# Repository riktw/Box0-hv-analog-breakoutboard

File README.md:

A breakout board for the Box0 so the Box0 is able to handle higher analog voltages
With this it can handle -33 to +33V on the input and output -33V to +33V as well.

The hardware is simple, 2 switching power supplies to boost the 5V in to +-33V, possible +-35V
After that 2 +-50V 50mA output capable opamps with a gain of 10 and a divide by 10 voltage devider so the analog inputs can handle +-33V as well

An USB port is added to supply the board with 5V as the 5V pin of the Box0 is unable to deliver enough current.
A small example:

10mA at 35V means that, at 100% efficiency, 70mA is needed at 5V, in practise this figure is closer to 90mA
With 2 opamps being capable of delivering 50mA a total of 100mA at 35V is required, meaning 900mA at 5V as input.

Current limit is implemented by using a 1A polyfuse, minimal but better then nothing. 

License: CC-SA-BY 4.0

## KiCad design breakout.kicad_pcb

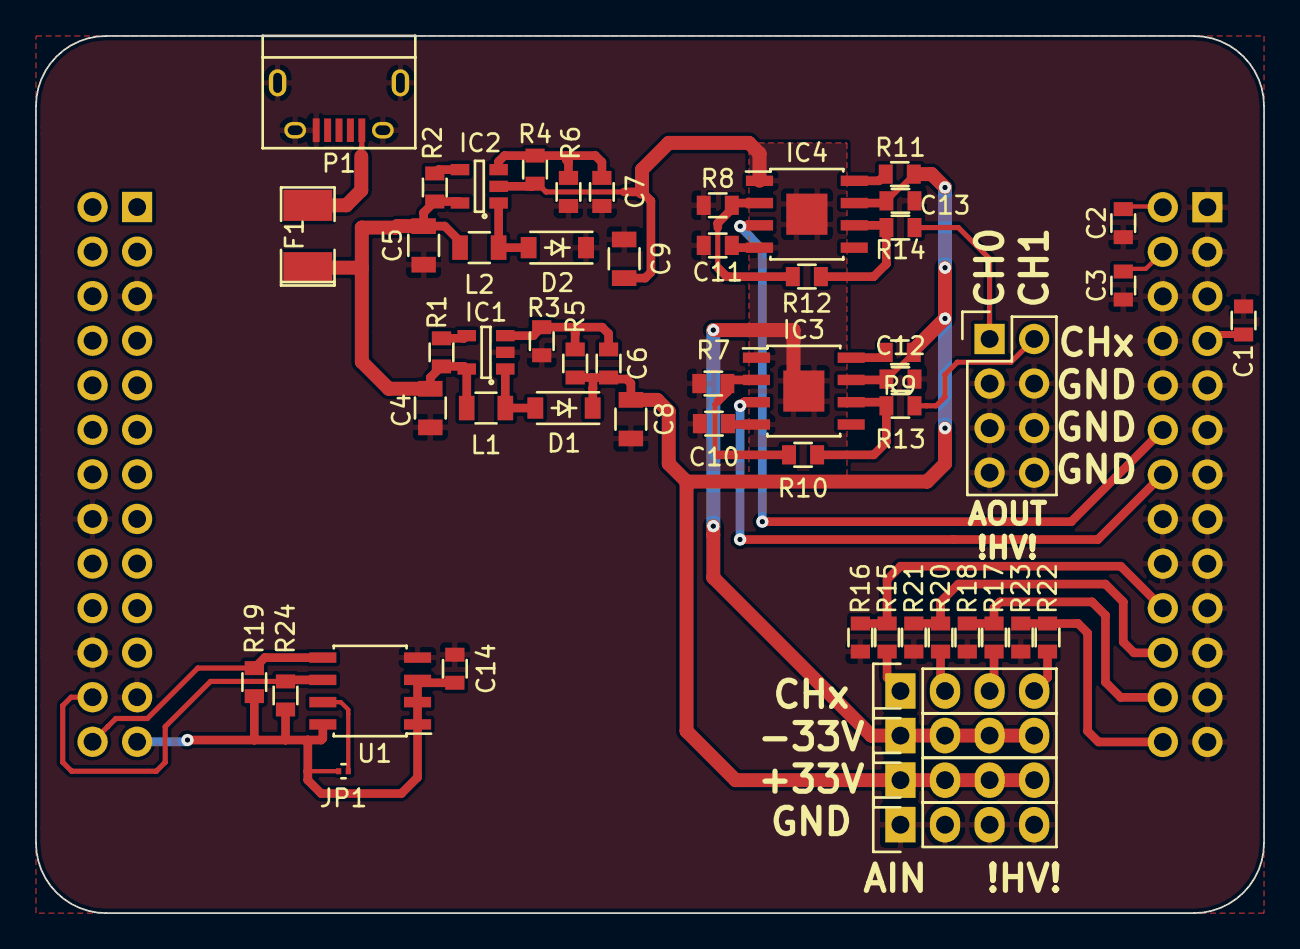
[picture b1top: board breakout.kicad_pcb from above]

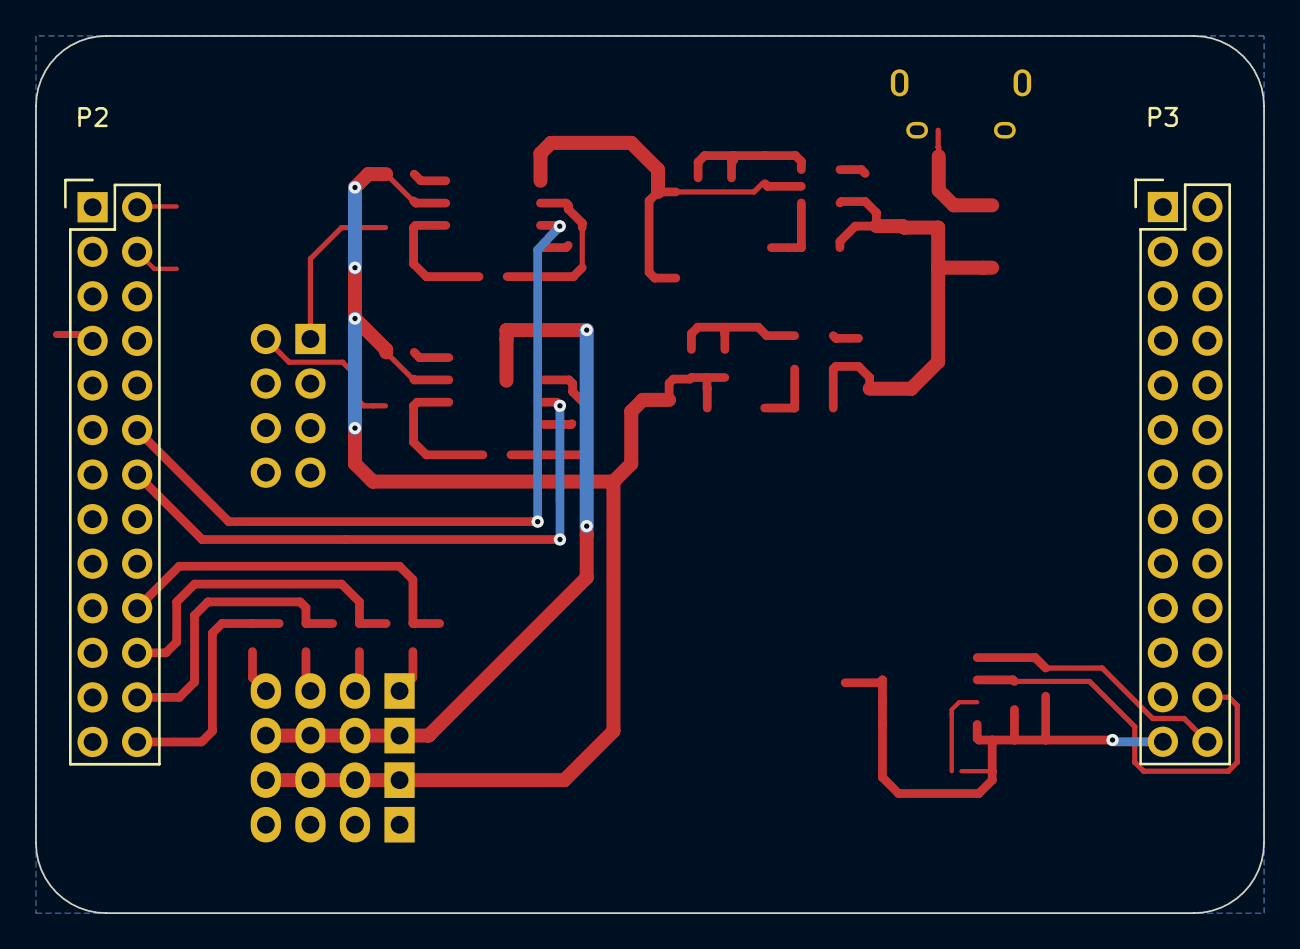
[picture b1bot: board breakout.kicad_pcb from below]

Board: 2 copper layers, 70.0 x 50.0 mm, 57 parts (2 on the bottom side), 36 nets.

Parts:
C1, C2, C3: 100nF; 0603
C4, C5: 4.7u; 0805
C6, C7: 82p; 0603
C8, C9: 10u; 0805
C10, C11, C12, C13, C14: 100n; 0603
D1, D2: MBR0540; SOD-123
F1: F_Small; SMD-1210_Pol
IC1, IC2: LM2733; SOT-23-5
IC3, IC4: OPA454; SOIC-8-3.9*4.9mm_HP_to_P4
JP1: Jumper_NO_Small; C_0201
L1, L2: 10u; 0805
P1: USB_OTG; USB_Micro-B
P2: BASE_BOARD_ANALOG; Pin_Header_Straight_2x13
P3: BASE_BOARD_DIGITAL; Pin_Header_Straight_2x13
P4: CONN_02X04; Pin_Header_Straight_2x04
P5, P6, P7, P8: CONN_01X04; Pin_Header_Straight_1x04
R1, R2: 47K; 0603
R3, R4: 12K; 0603
R5, R6: 309K; 0603
R7, R8, R16, R18, R21, R23: 10K; 0603
R9, R11: 1M; 0603
R10, R12, R15, R17, R20, R22: 91K; 0603
R13, R14: 10R; 0603
R19, R24: 4.7K; 0603
U1: 24C16; SOIC-8_3.9x4.9mm_Pitch1.27mm

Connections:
5V: C4.1, C5.1, F1.1, IC1.5, IC2.5, L1.2, L2.2, R1.1, R2.1
+33V: C6.2, C8.1, C12.1, C13.1, D1.1, IC3.7, IC4.7, P6.1, P6.2, P6.3, P6.4, R5.2, R9.1, R11.1
-33V: C9.2, C10.1, C11.1, IC2.2, IC3.1, IC3.4, IC4.1, IC4.4, P7.1, P7.2, P7.3, P7.4, R4.2
/Box0 Interface/AIN0.0: P2.20, R15.1, R16.2
/Box0 Interface/AIN0.1: P2.22, R20.1, R21.2
/Box0 Interface/AIN0.2: P2.24, R17.1, R18.2
/Box0 Interface/AIN0.3: P2.26, R22.1, R23.2
/Box0 Interface/AOUT0.0: IC4.3, P2.12
/Box0 Interface/AOUT0.1: IC3.3, P2.14
/Box0 Interface/I2C0.SCL: P3.24, R24.2, U1.6
/Box0 Interface/I2C0.SDA: P3.26, R19.2, U1.5
ANALOG_NEG: C3.1, P2.4
ANALOG_POS: C2.1, P2.2
DIGITAL_EXT: C14.1, JP1.1, P3.25, R19.1, R24.1, U1.1, U1.2, U1.3, U1.8
GND: C1.2, C2.2, C3.2, C4.2, C5.2, C7.2, C8.2, C9.1, C10.2, C11.2, C12.2, C13.2, C14.2, D2.1, IC1.2, P1.5, P1.6, P2.1, P2.3, P2.5, P2.6, P2.8, P2.9, P2.10, P2.11, P2.13, P2.15, P2.16, P2.17, P2.18, P2.19, P2.21, P2.23, P2.25, P3.5, P3.16, P3.22, P3.23, P4.3, P4.4, P4.5, P4.6, P4.7, P4.8, P5.1, P5.2, P5.3, P5.4, R3.2, R6.2, R7.1, R8.1, R16.1, R18.1, R21.1, R23.1, U1.4
unnamed: C6.1, IC1.3, R3.1, R5.1
unnamed: C7.1, IC2.3, R4.1, R6.1
unnamed: D1.2, IC1.1, L1.1
unnamed: D2.2, IC2.1, L2.1
unnamed: F1.2, P1.1
unnamed: IC1.4, R1.2
unnamed: IC2.4, R2.2
unnamed: IC3.2, R7.2, R10.2
unnamed: IC3.6, R10.1, R13.2
unnamed: IC3.8, R9.2
unnamed: IC4.2, R8.2, R12.2
unnamed: IC4.6, R12.1, R14.2
unnamed: IC4.8, R11.2
unnamed: JP1.2, U1.7
unnamed: P4.1, R14.1
unnamed: P4.2, R13.1
unnamed: P8.1, R15.2
unnamed: P8.2, R20.2
unnamed: P8.3, R17.2
unnamed: P8.4, R22.2
VREF_EXT: C1.1, P2.7

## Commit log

2016-12-17 First commit, empty breakout board
2016-12-18 Schematic nearly done
2016-12-18 Added license
2016-12-18 Started on PCB
2016-12-19 PCB almost done
2016-12-22 Finished PCB
2017-01-20 fixed the wrongly connected VREF
